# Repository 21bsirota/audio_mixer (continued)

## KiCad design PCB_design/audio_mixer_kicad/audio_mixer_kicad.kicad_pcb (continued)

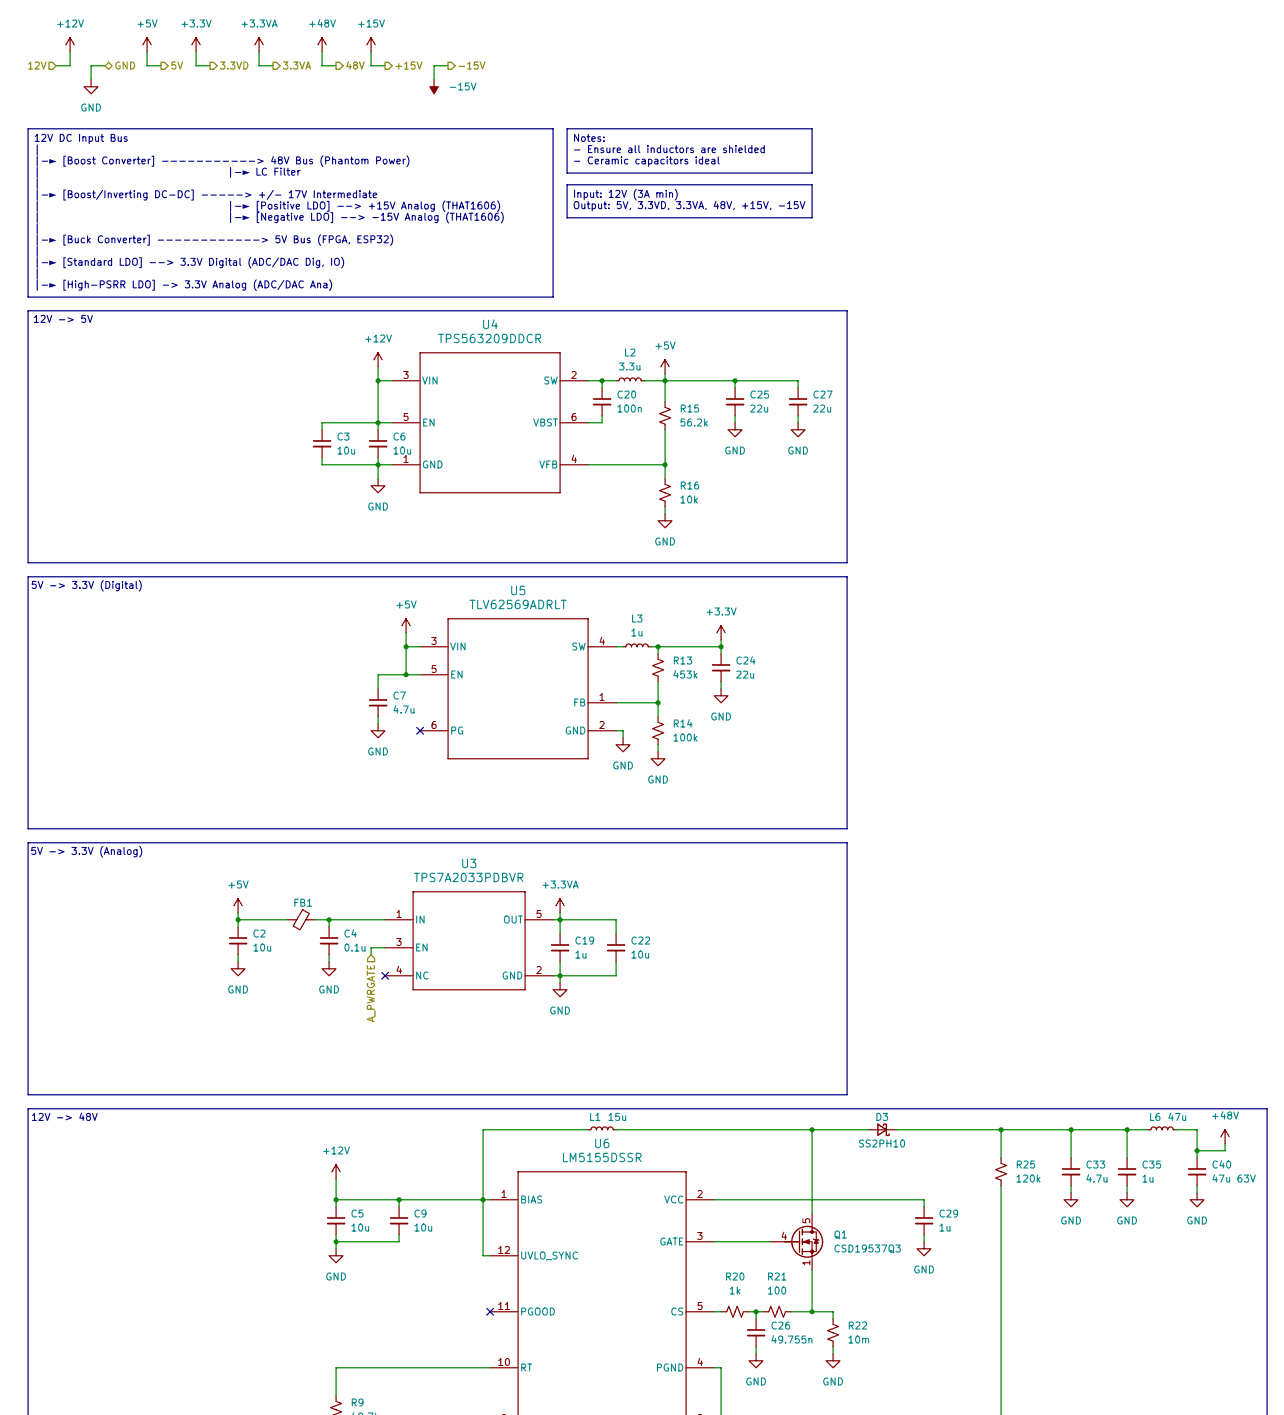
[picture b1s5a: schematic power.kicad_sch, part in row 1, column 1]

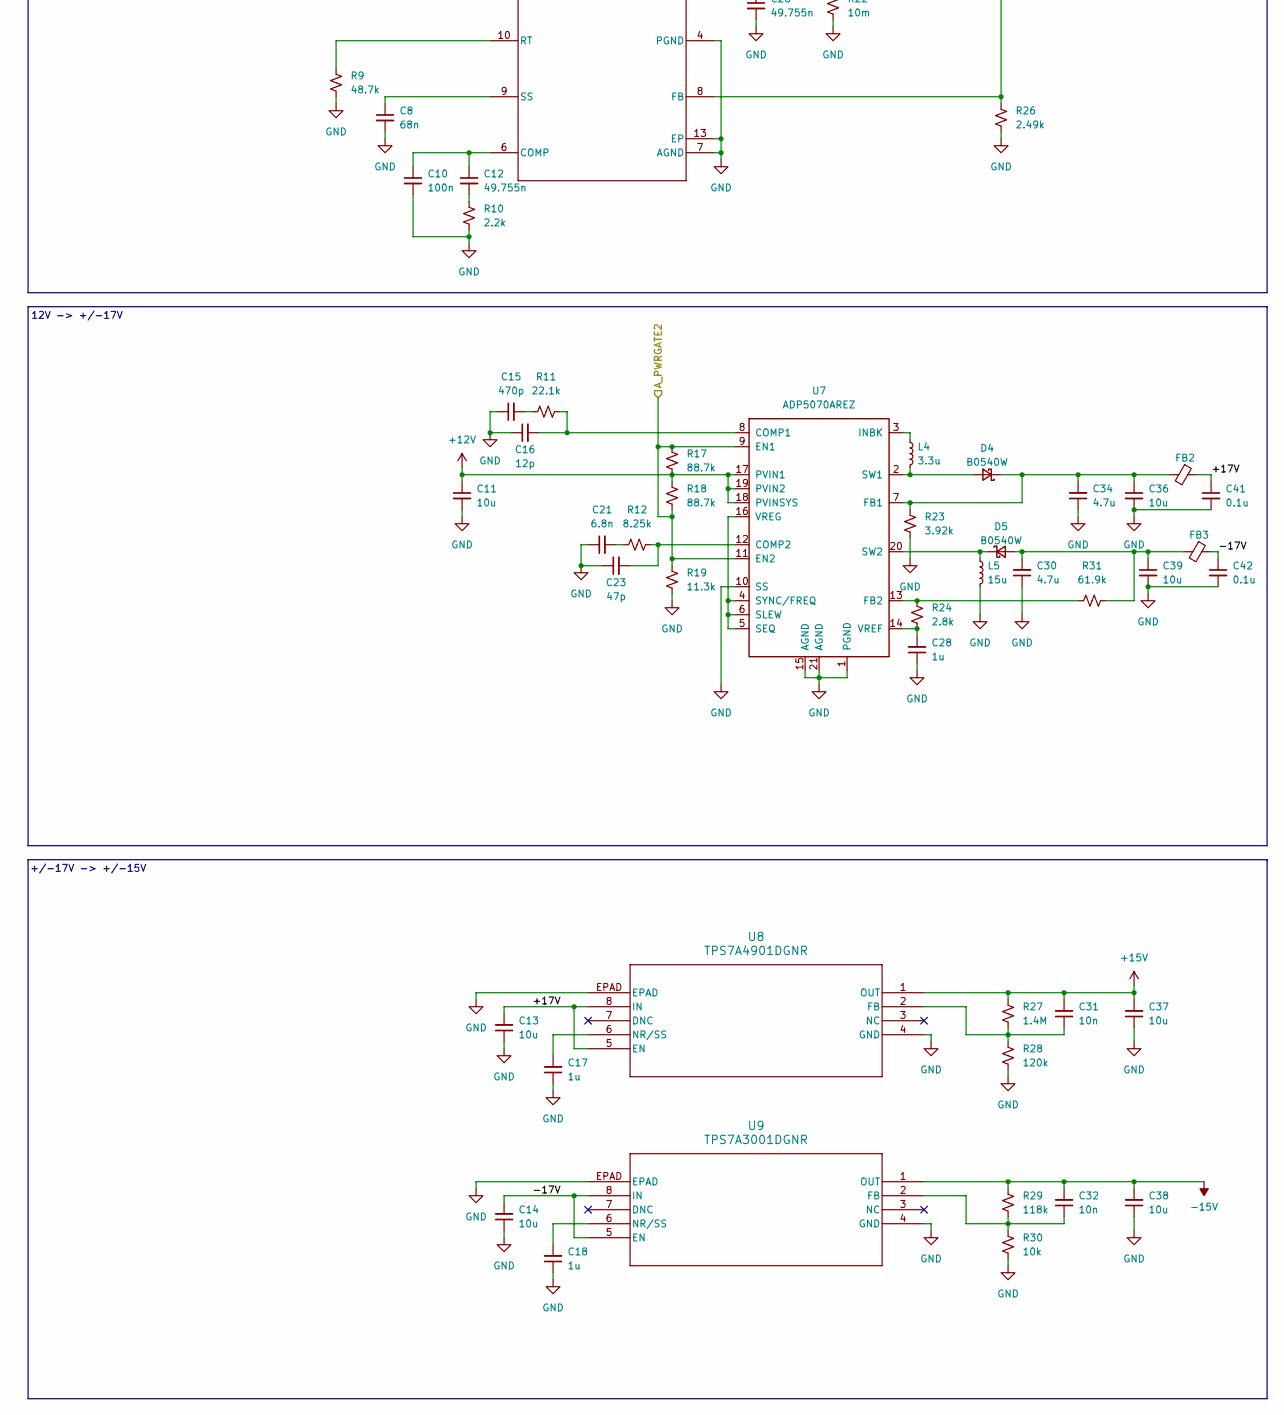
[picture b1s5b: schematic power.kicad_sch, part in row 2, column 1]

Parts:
C2, C3, C5, C6, C9, C11, C13, C14, C22, C36, C37, C38, C39: 10u; C_1206_3216Metric_Pad1.33x1.80mm_HandSolder
C4, C41, C42: 0.1u; C_1206_3216Metric_Pad1.33x1.80mm_HandSolder
C7, C30, C33, C34: 4.7u; C_1206_3216Metric_Pad1.33x1.80mm_HandSolder
C8: 68n; C_1206_3216Metric_Pad1.33x1.80mm_HandSolder
C10, C20: 100n; C_1206_3216Metric_Pad1.33x1.80mm_HandSolder
C12, C26: 49.755n; C_1206_3216Metric_Pad1.33x1.80mm_HandSolder
C15: 470p; C_1206_3216Metric_Pad1.33x1.80mm_HandSolder
C16: 12p; C_1206_3216Metric_Pad1.33x1.80mm_HandSolder
C17, C18, C19, C28, C29, C35: 1u; C_1206_3216Metric_Pad1.33x1.80mm_HandSolder
C21: 6.8n; C_1206_3216Metric_Pad1.33x1.80mm_HandSolder
C23: 47p; C_1206_3216Metric_Pad1.33x1.80mm_HandSolder
C24, C25, C27: 22u; C_1206_3216Metric_Pad1.33x1.80mm_HandSolder
C31, C32: 10n; C_1206_3216Metric_Pad1.33x1.80mm_HandSolder
C40: 47u 63V; C_1206_3216Metric_Pad1.33x1.80mm_HandSolder
D3: SS2PH10; DO-220AA_SS2PH10-M3&slash_84A_VIS
D4, D5: B0540W; SOD123_DIO-M
FB1, FB2, FB3: FerriteBead_Small; L_1206_3216Metric_Pad1.22x1.90mm_HandSolder
L1, L5: 15u; L_1206_3216Metric_Pad1.22x1.90mm_HandSolder
L2, L4: 3.3u; L_1206_3216Metric_Pad1.22x1.90mm_HandSolder
L3: 1u; L_1206_3216Metric_Pad1.22x1.90mm_HandSolder
L6: 47u; L_1206_3216Metric_Pad1.22x1.90mm_HandSolder
Q1: CSD19537Q3; VSON-8_3.3x3.3mm_P0.65mm_NexFET
R9: 48.7k; R_1206_3216Metric_Pad1.30x1.75mm_HandSolder
R10: 2.2k; R_1206_3216Metric_Pad1.30x1.75mm_HandSolder
R11: 22.1k; R_1206_3216Metric_Pad1.30x1.75mm_HandSolder
R12: 8.25k; R_1206_3216Metric_Pad1.30x1.75mm_HandSolder
R13: 453k; R_1206_3216Metric_Pad1.30x1.75mm_HandSolder
R14: 100k; R_1206_3216Metric_Pad1.30x1.75mm_HandSolder
R15: 56.2k; R_1206_3216Metric_Pad1.30x1.75mm_HandSolder
R16, R30: 10k; R_1206_3216Metric_Pad1.30x1.75mm_HandSolder
R17, R18: 88.7k; R_1206_3216Metric_Pad1.30x1.75mm_HandSolder
R19: 11.3k; R_1206_3216Metric_Pad1.30x1.75mm_HandSolder
R20: 1k; R_1206_3216Metric_Pad1.30x1.75mm_HandSolder
R21: 100; R_1206_3216Metric_Pad1.30x1.75mm_HandSolder
R22: 10m; R_1206_3216Metric_Pad1.30x1.75mm_HandSolder
R23: 3.92k; R_1206_3216Metric_Pad1.30x1.75mm_HandSolder
R24: 2.8k; R_1206_3216Metric_Pad1.30x1.75mm_HandSolder
R25, R28: 120k; R_1206_3216Metric_Pad1.30x1.75mm_HandSolder
R26: 2.49k; R_1206_3216Metric_Pad1.30x1.75mm_HandSolder
R27: 1.4M; R_1206_3216Metric_Pad1.30x1.75mm_HandSolder
R29: 118k; R_1206_3216Metric_Pad1.30x1.75mm_HandSolder
R31: 61.9k; R_1206_3216Metric_Pad1.30x1.75mm_HandSolder
U3: TPS7A2033PDBVR; DBV0005A-IPC_A
U4: TPS563209DDCR; DDC0006A
U5: TLV62569ADRLT; DRL0006A
U6: LM5155DSSR; DSS0012B
U7: ADP5070AREZ; ETSSOP-20-1EP_4.4x6.5mm_P0.65mm_EP3x4.2mm
U8: TPS7A4901DGNR; DGN8_1P89X1P57
U9: TPS7A3001DGNR; DGN8_1P89X1P57

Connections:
+3.3V: C24.1, L3.2, R13.1; also elsewhere on the board
+3.3VA: C19.1, C22.1, U3.5 (OUT); also elsewhere on the board
+5V: C2.1, C7.1, C25.1, C27.1, FB1.2, L2.2, R15.1, U5.3 (VIN), U5.5 (EN); also elsewhere on the board
+12V: C3.1, C5.1, C6.1, C9.1, C11.1, L1.1, R17.1, R18.2, U4.3 (VIN), U4.5 (EN), U6.1 (BIAS), U6.12 (UVLO_SYNC), U7.17 (PVIN1), U7.18 (PVINSYS), U7.19 (PVIN2); also elsewhere on the board
+15V: C31.2, C37.2, R27.2, U8.1 (OUT); also elsewhere on the board
+48V: C40.1, L6.2; also elsewhere on the board
-15V: C32.2, C38.2, R29.2, U9.1 (OUT); also elsewhere on the board
/A_PWRGATE: U3.3 (EN); also elsewhere on the board
/A_PWRGATE2: R17.2, R18.1, R19.2, U7.9 (EN1), U7.11 (EN2); also elsewhere on the board
/Power/+17V: C13.2, C41.1, FB2.1, U8.5 (EN), U8.8 (IN)
/Power/-17V: C14.2, C42.1, FB3.1, U9.5 (EN), U9.8 (IN)
GND: C2.2, C3.2, C4.2, C5.2, C6.2, C7.2, C8.2, C9.2, C10.2, C11.2, C13.1, C14.1, C15.1, C16.1, C17.1, C18.1, C19.2, C21.1, C22.2, C23.1, C24.2, C25.2, C26.2, C27.2, C28.1, C29.2, C30.1, C33.2, C34.1, C35.2, C36.2, C37.1, C38.1, C39.2, C40.2, C41.2, C42.2, L5.2, R9.2, R10.2, R14.2, R16.2, R19.1, R22.1, R23.1, R26.1, R28.1, R30.1, U3.2 (GND), U4.1 (GND), U5.2 (GND), U6.4 (PGND), U6.7 (AGND), U6.13 (EP), U7.1 (PGND), U7.10 (SS), U7.15 (AGND), U7.21 (AGND), U8.4 (GND), U8.EPAD, U9.4 (GND), U9.EPAD; also elsewhere on the board
unnamed: C12.2, R10.1
unnamed: C15.2, R11.1
unnamed: C21.2, R12.1
unnamed: C26.1, R20.2, R21.1
unnamed: D3.2 (A), L1.2, Q1.5 (D)
unnamed: C33.1, C35.1, D3.1 (K), L6.1, R25.2
unnamed: D4.2 (A), L4.2, U7.2 (SW1)
unnamed: C34.2, C36.1, D4.1 (K), FB2.2, R23.2, U7.7 (FB1)
unnamed: C30.2, C39.1, D5.2 (A), FB3.2, R31.1
unnamed: D5.1 (K), L5.1, U7.20 (SW2)
unnamed: Q1.4 (G), U6.3 (GATE)
unnamed: Q1.1 (S), Q1.2 (S), Q1.3 (S), R21.2, R22.2
unnamed: C4.1, FB1.1, U3.1 (IN)
unnamed: C20.1, L2.1, U4.2 (SW)
unnamed: C20.2, U4.6 (VBST)
unnamed: R15.2, R16.1, U4.4 (VFB)
unnamed: R13.2, R14.1, U5.1 (FB)
unnamed: L3.1, U5.4 (SW)
unnamed: C10.1, C12.1, U6.6 (COMP)
unnamed: R20.1, U6.5 (CS)
unnamed: R25.1, R26.2, U6.8 (FB)
unnamed: R9.1, U6.10 (RT)
unnamed: C8.1, U6.9 (SS)
unnamed: C29.1, U6.2 (VCC)
unnamed: C16.2, R11.2, U7.8 (COMP1)
unnamed: C23.2, R12.2, U7.12 (COMP2)
unnamed: R24.2, R31.2, U7.13 (FB2)
unnamed: L4.1, U7.3 (INBK)
unnamed: U7.4 (SYNC/FREQ), U7.5 (SEQ), U7.6 (SLEW), U7.16 (VREG)
unnamed: C28.2, R24.1, U7.14 (VREF)
unnamed: C31.1, R27.1, R28.2, U8.2 (FB)
unnamed: C17.2, U8.6 (NR/SS)
unnamed: C32.1, R29.1, R30.2, U9.2 (FB)
unnamed: C18.2, U9.6 (NR/SS)

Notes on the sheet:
12V -> 48V
12V -> 5V
5V -> 3.3V (Analog)
12V -> +/-17V
+/-17V -> +/-15V
5V -> 3.3V (Digital)
Notes: - Ensure all inductors are shielded - Ceramic capacitors ideal
12V DC Input Bus | |-► [Boost Converter] -----------> 48V Bus (Phantom Power) | |-► LC Filter | |-► [Boost/Inverting DC-DC] -----> +/- 17V Intermediate | |-► [Positive LDO] --> +15V Analog (THAT1606) | |-► [Negative LDO] --> -15V Analog (THAT1606) | |-► [Buck Converter] ------------> 5V Bus (FPGA, 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
Input: 12V (3A min) Output: 5V, 3.3VD, 3.3VA, 48V, +15V, -15V

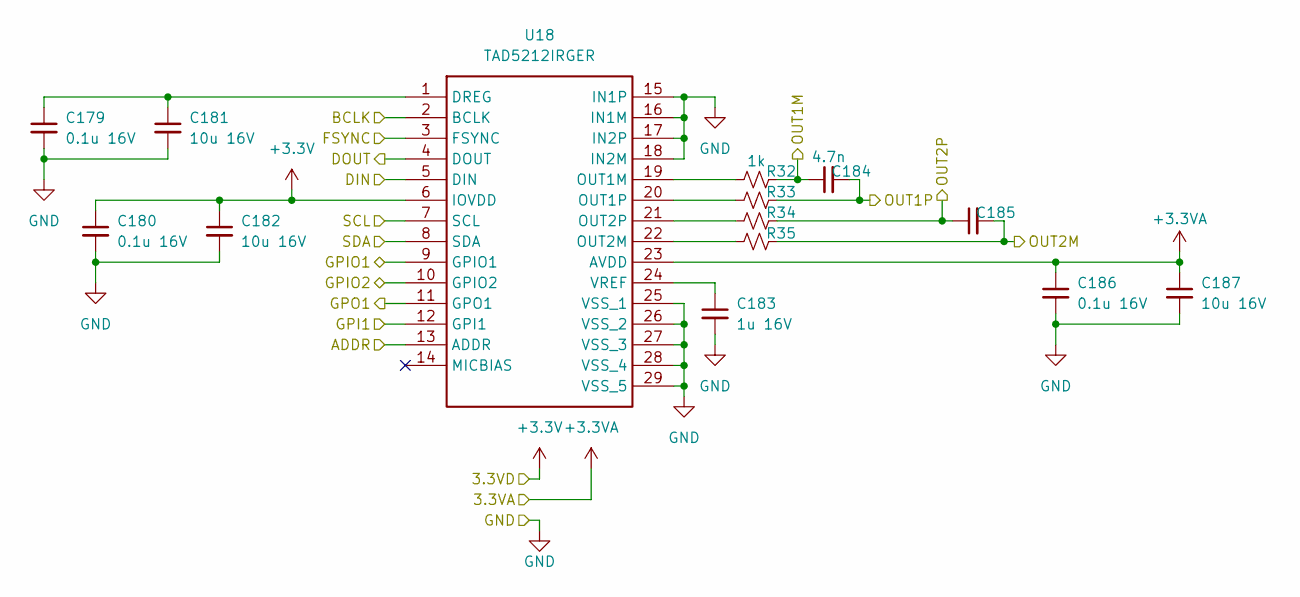
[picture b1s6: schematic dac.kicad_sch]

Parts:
C179, C180, C186: 0.1u 16V; C_1206_3216Metric_Pad1.33x1.80mm_HandSolder
C181, C182, C187: 10u 16V; C_1206_3216Metric_Pad1.33x1.80mm_HandSolder
C183: 1u 16V; C_1206_3216Metric_Pad1.33x1.80mm_HandSolder
C184, C185: 4.7n; C_1206_3216Metric_Pad1.33x1.80mm_HandSolder
R32, R33, R34, R35: 1k; R_1206_3216Metric_Pad1.30x1.75mm_HandSolder
U18: TAD5212IRGER; Mouser Part Number 595-TAD5212IRGER

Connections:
+3.3V: C180.1, C182.1, U18.6 (IOVDD); also elsewhere on the board
+3.3VA: C186.1, C187.1, U18.23 (AVDD); also elsewhere on the board
/BCLK: U18.2 (BCLK); also elsewhere on the board
/DAC0/ADDR: U18.13 (ADDR); also elsewhere on the board
/DAC0/DOUT: U18.4 (DOUT)
/DAC0/GPIO1: U18.9 (GPIO1); also elsewhere on the board
/DAC0/GPIO2: U18.10 (GPIO2); also elsewhere on the board
/DAC0/GPO1: U18.11 (GPO1); also elsewhere on the board
/DAC0/OUT1M: C184.1, R32.2; also elsewhere on the board
/DAC0/OUT1P: C184.2, R33.2; also elsewhere on the board
/DAC0/OUT2M: C185.2, R35.2; also elsewhere on the board
/DAC0/OUT2P: C185.1, R34.2; also elsewhere on the board
/DIN0: U18.5 (DIN); also elsewhere on the board
/FSYNC: U18.3 (FSYNC); also elsewhere on the board
/I2C0_SCL: U18.7 (SCL); also elsewhere on the board
/I2C0_SDA: U18.8 (SDA); also elsewhere on the board
/MCLK: U18.12 (GPI1); also elsewhere on the board
GND: C179.2, C180.2, C181.2, C182.2, C183.2, C186.2, C187.2, U18.15 (IN1P), U18.16 (IN1M), U18.17 (IN2P), U18.18 (IN2M), U18.25 (VSS_1), U18.26 (VSS_2), U18.27 (VSS_3), U18.28 (VSS_4), U18.29 (VSS_5); also elsewhere on the board
unnamed: C179.1, C181.1, U18.1 (DREG)
unnamed: R32.1, U18.19 (OUT1M)
unnamed: R33.1, U18.20 (OUT1P)
unnamed: R35.1, U18.22 (OUT2M)
unnamed: R34.1, U18.21 (OUT2P)
unnamed: C183.1, U18.24 (VREF)

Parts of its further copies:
C188, C189, C195: 0.1u 16V; C_1206_3216Metric_Pad1.33x1.80mm_HandSolder
C190, C191, C196: 10u 16V; C_1206_3216Metric_Pad1.33x1.80mm_HandSolder
C192: 1u 16V; C_1206_3216Metric_Pad1.33x1.80mm_HandSolder
C193, C194: 4.7n; C_1206_3216Metric_Pad1.33x1.80mm_HandSolder
R36, R37, R38, R39: 1k; R_1206_3216Metric_Pad1.30x1.75mm_HandSolder
U19: TAD5212IRGER; Mouser Part Number 595-TAD5212IRGER

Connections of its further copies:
+3.3V: C189.1, C191.1, U19.6 (IOVDD); also elsewhere on the board
+3.3VA: C195.1, C196.1, U19.23 (AVDD); also elsewhere on the board
/BCLK: U19.2 (BCLK); also elsewhere on the board
/DAC1/ADDR: U19.13 (ADDR); also elsewhere on the board
/DAC1/DOUT: U19.4 (DOUT)
/DAC1/GPIO1: U19.9 (GPIO1); also elsewhere on the board
/DAC1/GPIO2: U19.10 (GPIO2); also elsewhere on the board
/DAC1/GPO1: U19.11 (GPO1); also elsewhere on the board
/DAC1/OUT1M: C193.1, R36.2; also elsewhere on the board
/DAC1/OUT1P: C193.2, R37.2; also elsewhere on the board
/DAC1/OUT2M: C194.2, R39.2; also elsewhere on the board
/DAC1/OUT2P: C194.1, R38.2; also elsewhere on the board
/DIN1: U19.5 (DIN); also elsewhere on the board
/FSYNC: U19.3 (FSYNC); also elsewhere on the board
/I2C1_SCL: U19.7 (SCL); also elsewhere on the board
/I2C1_SDA: U19.8 (SDA); also elsewhere on the board
/MCLK: U19.12 (GPI1); also elsewhere on the board
GND: C188.2, C189.2, C190.2, C191.2, C192.2, C195.2, C196.2, U19.15 (IN1P), U19.16 (IN1M), U19.17 (IN2P), U19.18 (IN2M), U19.25 (VSS_1), U19.26 (VSS_2), U19.27 (VSS_3), U19.28 (VSS_4), U19.29 (VSS_5); also elsewhere on the board
unnamed: C188.1, C190.1, U19.1 (DREG)
unnamed: R36.1, U19.19 (OUT1M)
unnamed: R37.1, U19.20 (OUT1P)
unnamed: R39.1, U19.22 (OUT2M)
unnamed: R38.1, U19.21 (OUT2P)
unnamed: C192.1, U19.24 (VREF)

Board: 4 copper layers, 792 parts (0 on the bottom side), 418 nets, no tracks yet.

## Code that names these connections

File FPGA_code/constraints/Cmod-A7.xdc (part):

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
## GPIO Pins
## Pins 15 and 16 should remain commented if using them as analog inputs
set_property -dict { PACKAGE_PIN M3    IOSTANDARD LVCMOS33 } [get_ports { MCLK  }]; #IO_L8N_T1_AD14N_35 Sch=pio[01]
set_property -dict { PACKAGE_PIN L3    IOSTANDARD LVCMOS33 } [get_ports { FSYNC }]; #IO_L8P_T1_AD14P_35 Sch=pio[02]
set_property -dict { PACKAGE_PIN A16   IOSTANDARD LVCMOS33 } [get_ports { BCLK  }]; #IO_L12P_T1_MRCC_16 Sch=pio[03]
set_property -dict { PACKAGE_PIN K3    IOSTANDARD LVCMOS33 } [get_ports { SDOUT0  }]; #IO_L7N_T1_AD6N_35 Sch=pio[04]
set_property -dict { PACKAGE_PIN C15   IOSTANDARD LVCMOS33 } [get_ports { SDOUT1  }]; #IO_L11P_T1_SRCC_16 Sch=pio[05]
set_property -dict { PACKAGE_PIN H1    IOSTANDARD LVCMOS33 } [get_ports { SDOUT2  }]; #IO_L3P_T0_DQS_AD5P_35 Sch=pio[06]
set_property -dict { PACKAGE_PIN A15   IOSTANDARD LVCMOS33 } [get_ports { SDOUT3  }]; #IO_L6N_T0_VREF_16 Sch=pio[07]
set_property -dict { PACKAGE_PIN B15   IOSTANDARD LVCMOS33 } [get_ports { SDOUT4  }]; #IO_L11N_T1_SRCC_16 Sch=pio[08]
set_property -dict { PACKAGE_PIN A14   IOSTANDARD LVCMOS33 } [get_ports { SDOUT5  }]; #IO_L6P_T0_16 Sch=pio[09]
set_property -dict { PACKAGE_PIN J3    IOSTANDARD LVCMOS33 } [get_ports { SDOUT6 }]; #IO_L7P_T1_AD6P_35 Sch=pio[10]
set_property -dict { PACKAGE_PIN J1    IOSTANDARD LVCMOS33 } [get_ports { SDOUT7 }]; #IO_L3N_T0_DQS_AD5N_35 Sch=pio[11]
#set_property -dict { PACKAGE_PIN K2    IOSTANDARD LVCMOS33 } [get_ports { pio12 }]; #IO_L5P_T0_AD13P_35 Sch=pio[12]
#set_property -dict { PACKAGE_PIN L1    IOSTANDARD LVCMOS33 } [get_ports { pio13 }]; #IO_L6N_T0_VREF_35 Sch=pio[13]
#set_property -dict { PACKAGE_PIN L2    IOSTANDARD LVCMOS33 } [get_ports { pio14 }]; #IO_L5N_T0_AD13N_35 Sch=pio[14]
set_property -dict { PACKAGE_PIN M1    IOSTANDARD LVCMOS33 } [get_ports { TX }]; #IO_L9N_T1_DQS_AD7N_35 Sch=pio[17]
set_property -dict { PACKAGE_PIN N3    IOSTANDARD LVCMOS33 } [get_ports { RX }]; #IO_L12P_T1_MRCC_35 Sch=pio[18]
set_property -dict { PACKAGE_PIN P3    IOSTANDARD LVCMOS33 } [get_ports { RST_N }]; #IO_L12N_T1_MRCC_35 Sch=pio[19]
set_property -dict { PACKAGE_PIN M2    IOSTANDARD LVCMOS33 } [get_ports { FPGA_CS }]; #IO_L9P_T1_DQS_AD7P_35 Sch=pio[20]
set_property -dict { PACKAGE_PIN N1    IOSTANDARD LVCMOS33 } [get_ports { MOSI }]; #IO_L10N_T1_AD15N_35 Sch=pio[21]
set_property -dict { PACKAGE_PIN N2    IOSTANDARD LVCMOS33 } [get_ports { MISO }]; #IO_L10P_T1_AD15P_35 Sch=pio[22]
set_property -dict { PACKAGE_PIN P1    IOSTANDARD LVCMOS33 } [get_ports { SCK }]; #IO_L19N_T3_VREF_35 Sch=pio[23]
set_property -dict { PACKAGE_PIN R3    IOSTANDARD LVCMOS33 } [get_ports { A_PWRGATE }]; #IO_L2P_T0_34 Sch=pio[26]
set_property -dict { PACKAGE_PIN T3    IOSTANDARD LVCMOS33 } [get_ports { A_PWRGATE2 }]; #IO_L2N_T0_34 Sch=pio[27]
#set_property -dict { PACKAGE_PIN R2    IOSTANDARD LVCMOS33 } [get_ports { pio28 }]; #IO_L1P_T0_34 Sch=pio[28]
set_property -dict { PACKAGE_PIN T1    IOSTANDARD LVCMOS33 } [get_ports { CLK_STANDBY }]; #IO_L3P_T0_DQS_34 Sch=pio[29]
set_property -dict { PACKAGE_PIN T2    IOSTANDARD LVCMOS33 } [get_ports { OSC_CLK }]; #IO_L1N_T0_34 Sch=pio[30]
#set_property -dict { PACKAGE_PIN U1    IOSTANDARD LVCMOS33 } [get_ports { pio31 }]; #IO_L3N_T0_DQS_34 Sch=pio[31]
set_property -dict { PACKAGE_PIN W2    IOSTANDARD LVCMOS33 } [get_ports { I2C0_SCL }]; #IO_L5N_T0_34 Sch=pio[32]
set_property -dict { PACKAGE_PIN V2    IOSTANDARD LVCMOS33 } [get_ports { I2C0_SDA }]; #IO_L5P_T0_34 Sch=pio[33]
set_property -dict { PACKAGE_PIN W3    IOSTANDARD LVCMOS33 } [get_ports { I2C1_SCL }]; #IO_L6N_T0_VREF_34 Sch=pio[34]
set_property -dict { PACKAGE_PIN V3    IOSTANDARD LVCMOS33 } [get_ports { I2C1_SDA }]; #IO_L6P_T0_34 Sch=pio[35]
#set_property -dict { PACKAGE_PIN W5    IOSTANDARD LVCMOS33 } [get_ports { pio36 }]; #IO_L12P_T1_MRCC_34 Sch=pio[36]
#set_property -dict { PACKAGE_PIN V4    IOSTANDARD LVCMOS33 } [get_ports { pio37 }]; #IO_L11N_T1_SRCC_34 Sch=pio[37]
#set_property -dict { PACKAGE_PIN U4    IOSTANDARD LVCMOS33 } [get_ports { pio38 }]; #IO_L11P_T1_SRCC_34 Sch=pio[38]
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#set_property -dict { PACKAGE_PIN U3    IOSTANDARD LVCMOS33 } [get_ports { pio44 }]; #IO_L9P_T1_DQS_34 Sch=pio[44]
#set_property -dict { PACKAGE_PIN U7    IOSTANDARD LVCMOS33 } [get_ports { pio45 }]; #IO_L19P_T3_34 Sch=pio[45]
#set_property -dict { PACKAGE_PIN W7    IOSTANDARD LVCMOS33 } [get_ports { pio46 }]; #IO_L13P_T2_MRCC_34 Sch=pio[46]
set_property -dict { PACKAGE_PIN U8    IOSTANDARD LVCMOS33 } [get_ports { DIN1 }]; #IO_L14P_T2_SRCC_34 Sch=pio[47]
set_property -dict { PACKAGE_PIN V8    IOSTANDARD LVCMOS33 } [get_ports { DIN0 }]; #IO_L14N_T2_SRCC_34 Sch=pio[48]

## UART
#set_property -dict { PACKAGE_PIN J18   IOSTANDARD LVCMOS33 } [get_ports { uart_rxd_out }]; #IO_L7N_T1_D10_14 Sch=uart_rxd_out
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
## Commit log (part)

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2026-06-18 Add initial audio mixer project files
    Add full project scaffold for the audio mixer hardware and firmware. Includes FPGA sources (clock wizard IP, constraints XDC, simulation testbench, and SV modules: audio_mixer, param_bram, spi_interf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
2026-06-21 Add libraries and models
2026-06-26 Schematics v1
2026-06-26 Add oscillator and adc input caps
2026-06-26 Reannotate and add passives for Y1
2026-06-28 Route I2C to FPGA
2026-06-30 Move I2C pins away from FPGA analog ports
